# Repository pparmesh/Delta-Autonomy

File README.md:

# Software stack for Collision Avoidance System developed by Delta Autonomy

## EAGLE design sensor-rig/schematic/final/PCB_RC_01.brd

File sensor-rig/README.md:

# Sensor Rig
Repository for keeping sensor rig firmware and data acquisition scripts

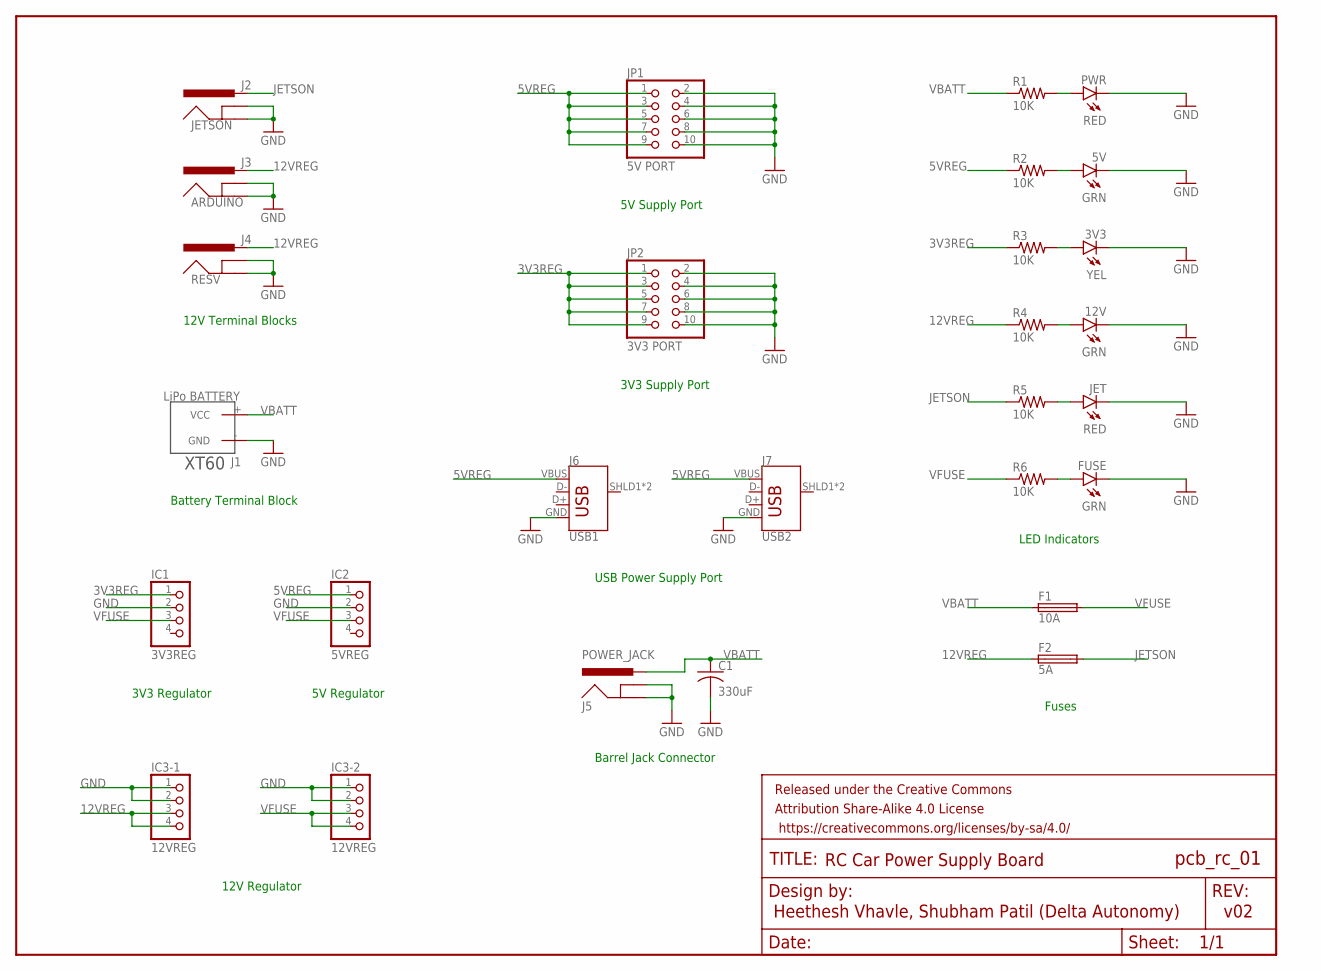
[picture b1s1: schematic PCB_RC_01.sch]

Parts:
3V3: YEL; LED3MM
5V, 12V: GRN; LED3MM
C1: 330uF; C025-050X050
F1: 10A; FUSE_HOLDER_5X20MM
F2: 5A; FUSE_HOLDER_5X20MM
FRAME1: FRAME-LETTERNO_PACKAGE; DUMMY
FUSE: GRN; LED3MM
IC1: 3V3REG; 1X04
IC2: 5VREG; 1X04
IC3-1, IC3-2: 12VREG; 1X04
J1: LiPo BATTERY; XT60
J2: JETSON; POWER_JACK_PTH
J3: ARDUINO; POWER_JACK_PTH
J4: RESV; POWER_JACK_PTH
J5: POWER_JACK; POWER_JACK_PTH
J6: USB1; USB-B-PTH
J7: USB2; USB-B-PTH
JET: RED; LED3MM
JP1: 5V PORT; 2X05
JP2: 3V3 PORT; 2X05
PWR: RED; LED3MM
R1, R2, R3, R4, R5, R6: 10K; V234/12

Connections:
3V3REG: IC1.1, JP2.1, JP2.3, JP2.5, JP2.7, JP2.9, R3.1
5VREG: IC2.1, J6.VBUS, J7.VBUS, JP1.1, JP1.3, JP1.5, JP1.7, JP1.9, R2.1
12VREG: F2.1, IC3-1.3, IC3-1.4, J3.PWR, J4.PWR, R4.1
GND: 3V3.K (C), 5V.K (C), 12V.K (C), C1.2, FUSE.K (C), IC1.2, IC2.2, IC3-1.1, IC3-1.2, IC3-2.1, IC3-2.2, J1.- (GND), J2.GND, J2.GNDBREAK, J3.GND, J3.GNDBREAK, J4.GND, J4.GNDBREAK, J5.GND, J5.GNDBREAK, J6.GND, J7.GND, JET.K (C), JP1.2, JP1.4, JP1.6, JP1.8, JP1.10, JP2.2, JP2.4, JP2.6, JP2.8, JP2.10, PWR.K (C)
JETSON: F2.2, J2.PWR, R5.1
unnamed: PWR.A, R1.2
unnamed: 5V.A, R2.2
unnamed: 3V3.A, R3.2
unnamed: 12V.A, R4.2
unnamed: JET.A, R5.2
unnamed: FUSE.A, R6.2
VBATT: C1.1, F1.1, J1.+ (VCC), J5.PWR, R1.1
VFUSE: F1.2, IC1.3, IC2.3, IC3-2.3, IC3-2.4, R6.1

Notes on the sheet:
Fuses
LED Indicators
3V3 Supply Port
5V Supply Port
USB Power Supply Port
Battery Terminal Block
12V Terminal Blocks
5V Regulator
12V Regulator
3V3 Regulator
Heethesh Vhavle, Shubham Patil (Delta Autonomy)
Barrel Jack Connector
v02
RC Car Power Supply Board

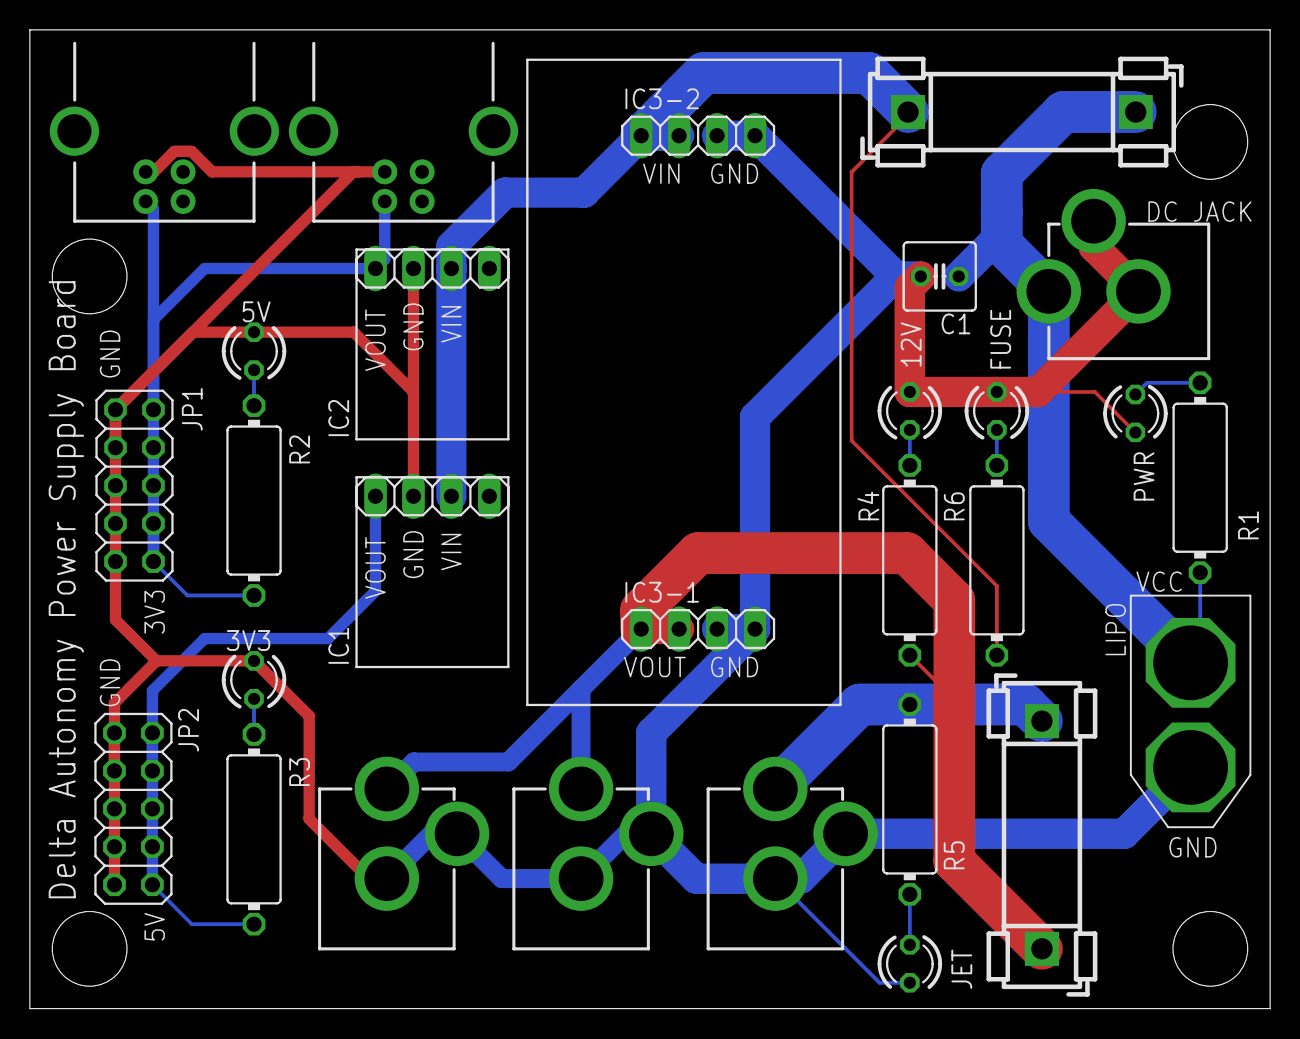
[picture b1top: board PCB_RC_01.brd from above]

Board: 2 copper layers, 83.0 x 65.5 mm, 29 parts (0 on the bottom side), 13 nets.

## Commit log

2019-12-15 Capstone

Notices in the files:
parts and their libraries:
SparkFun-Connectors: Licensing: Creative Commons ShareAlike 4.0 International - https://creativecommons.org/licenses/by-sa/4.0
SparkFun-Aesthetics: Released under the Creative Commons Attribution Share-Alike 4.0 License
SparkFun-Aesthetics: https://creativecommons.org/licenses/by-sa/4.0
